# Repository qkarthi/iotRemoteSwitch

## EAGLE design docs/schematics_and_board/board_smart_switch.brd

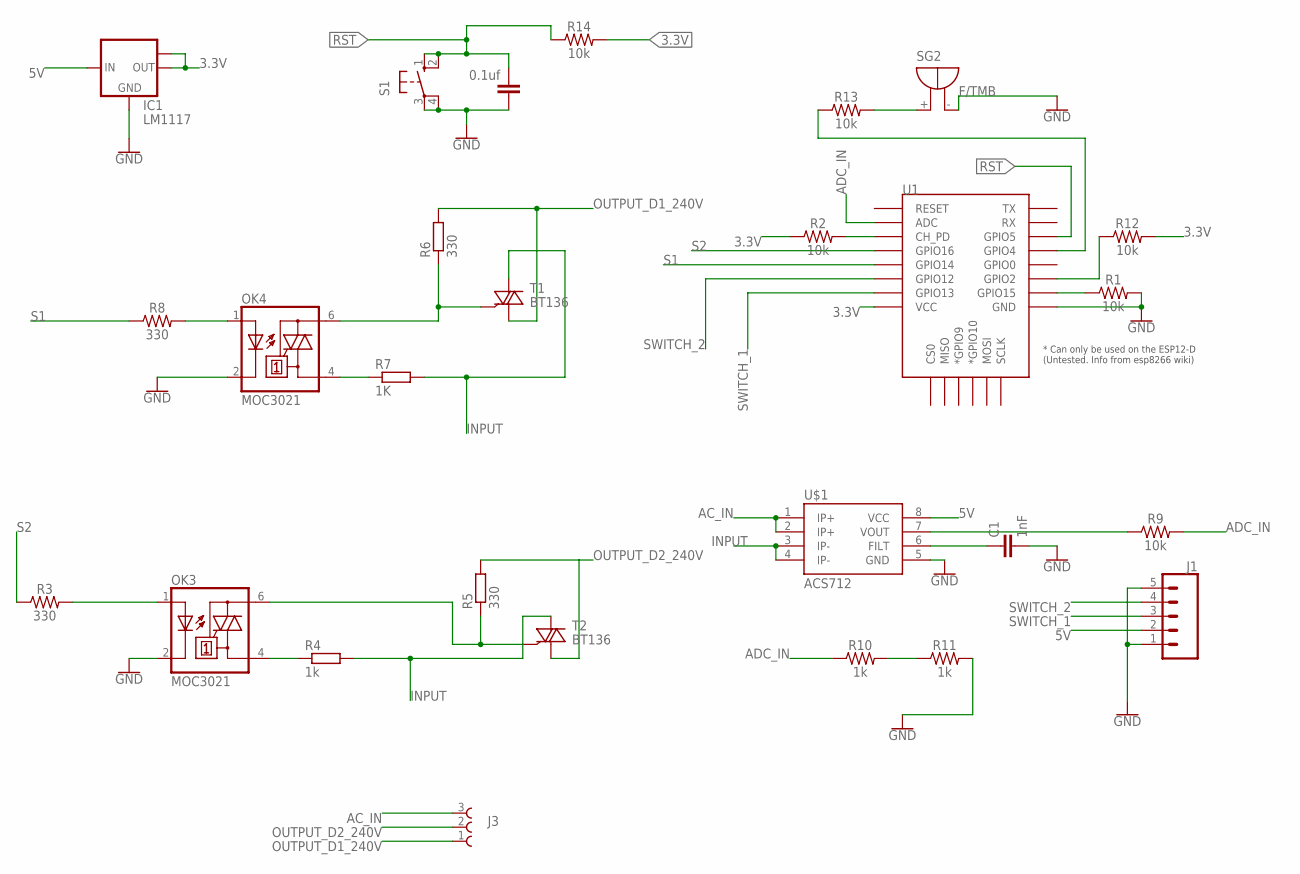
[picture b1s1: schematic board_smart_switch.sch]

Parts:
C1: 1nF; 0805
C2: 0.1uf; 0805
IC1: LM1117; SOT223
J1: CONN_05JST; JST-5-PTH
J3: 691104700003
OK3, OK4: MOC3021; DIL6-SMD
R1, R2, R9, R12, R13, R14: 10k; 0805
R3, R8: 330; 0805
R4: 1k; R2512
R5, R6: 330; R2512
R7: 1K; R2512
R10, R11: 1k; 0805
S1: 10-XX; B3F-10XX
SG2: F/TMB
T1, T2: BT136; TO220AB
U1: ESP12ESMD; ESP12E-SMD
U$1: ACS712; SO08

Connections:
3.3V: IC1.2 (OUT), IC1.TAB (OUT1), R2.1, R12.2, R14.2, U1.VCC
5V: IC1.3 (IN), J1.2, U$1.8 (VCC)
AC_IN: J3.3 (1), U$1.1 (IP+), U$1.2 (IP+)
ADC_IN: R9.2, R10.1, U1.ADC
GND: C1.2, C2.1, IC1.1 (GND), J1.1, J1.5, OK3.2 (C), OK4.2 (C), R1.2, R11.2, S1.3, S1.4 (P1), SG2.-, U1.GND, U$1.5 (GND)
INPUT: R4.2, R7.2, T1.2 (A2), T2.2 (A2), U$1.3 (IP-), U$1.4 (IP-)
unnamed: OK4.1 (A), R8.2
unnamed: OK3.1 (A), R3.2
unnamed: R2.2, U1.CH_PD
unnamed: R1.1, U1.GPIO15
unnamed: OK4.4 (A1), R7.1
unnamed: OK3.6 (A2), R5.1, T2.3 (G)
unnamed: C1.1, U$1.6 (FILT)
unnamed: OK3.4 (A1), R4.1
unnamed: OK4.6 (A2), R6.1, T1.3 (G)
unnamed: R9.1, U$1.7 (VOUT)
unnamed: R10.2, R11.1
unnamed: R12.1, U1.GPIO2
unnamed: R13.2, SG2.+
unnamed: R13.1, U1.GPIO4
OUTPUT_D1_240V: J3.1 (3), R6.2, T1.1 (A1)
OUTPUT_D2_240V: J3.2, R5.2, T2.1 (A1)
RST: C2.2, R14.1, S1.1 (S), S1.2 (S1), U1.GPIO5
S1: R8.1, U1.GPIO14
S2: R3.1, U1.GPIO16
SWITCH_1: J1.3, U1.GPIO13
SWITCH_2: J1.4, U1.GPIO12

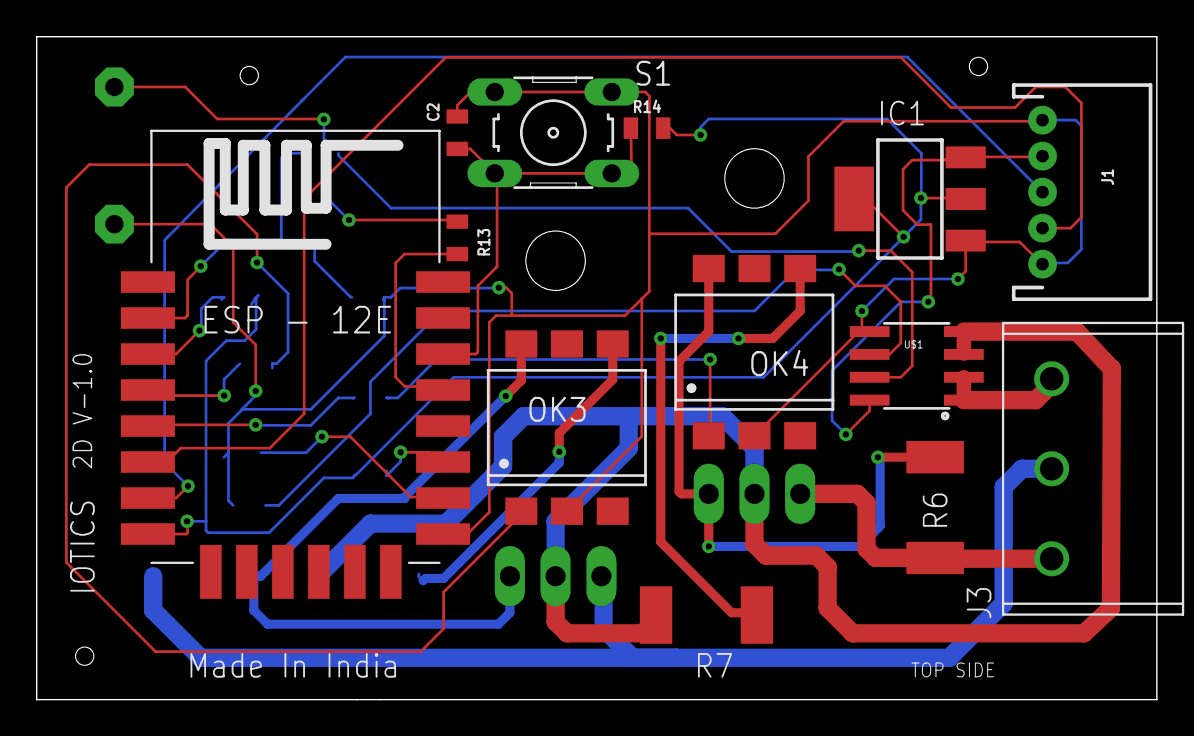
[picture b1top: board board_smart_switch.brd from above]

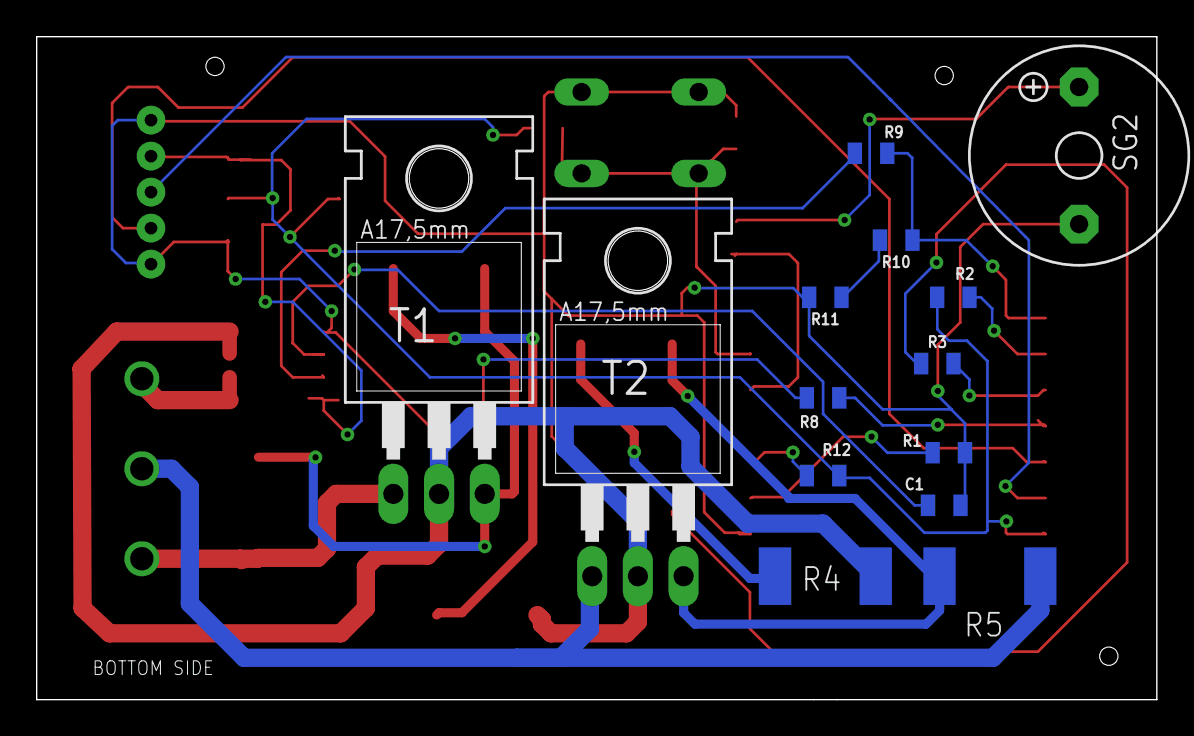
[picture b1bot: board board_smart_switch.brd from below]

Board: 2 copper layers, 62.2 x 36.8 mm, 27 parts (14 on the bottom side), 27 nets.

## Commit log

2017-08-04 Initial commit to repo
2017-08-04 added to git
2017-08-04 board_details
2017-08-08 RESET CODE
2017-08-08 RESET CODE successfully integrated
2017-08-08 RESET CODE updated
2017-08-18 commented
2017-08-21 unit/watts calculation
2017-08-28 new file testing
2017-08-28 new text
2017-08-28 buzzer code added
2017-08-29 buzzer code added and verified
2017-09-02 upto date
2017-09-06 code bare esp8266
2017-09-08 schedular_user_informative
2017-09-11 schedular_rev_1
2017-09-12 bare medium firmware v 1.0
2017-09-12 error rectified on scheduling
2017-09-14 kw hr calculation with reset
2017-09-19 mac address to wifi ssid
2017-10-06 karthik upto date all codes
2017-10-09 reset prevention
2017-10-11 alpha_version_firmware_cloud_rtc
2017-10-20 arduino and esp combination via serial slazer
2018-03-05 Added Templeate ID and variable
2018-04-23 New repo initialized
2018-04-23 directory removed
2018-05-05 Blynk connection check
2018-05-07 Refactor code for offline devices
2018-05-07 dump switch state to device
2018-05-08 dump mode real time code added
2018-05-08 last memory state of device retained
2018-05-08 switch state changer identification
2018-05-09 dump + last state + reset
2018-05-09 timeout for ap mode
2018-05-09 timeout for ap mode correction
2018-05-10 added disconnection and blynk reconnection code
2018-05-11 rssi + status icon + scheduling + wifi timeadjust )
2018-05-15 disabled wifi cloud checking
2018-05-15 last state added to branch
2018-05-15 2.4.1 library finished
2018-05-16 device s=tiles status fixed
2018-05-22 hard code for single device
2018-05-22 device show for upnp
2018-05-22 working for one device - cleaned after removing wrong functions
2018-05-23 added codes in linear method
2018-05-23 alexa working with blynk for 2 devices
2018-05-23 alexa functions completed and checked
2018-05-24 updated wemo switch serial number
2018-05-28 string for bulb is introduced
2018-05-29 device renaming via text box
2018-06-11 debug code enhanced
2018-07-16 vendor,board,firmware changed
2018-07-23 code upgrade
2019-04-22 migrated to github

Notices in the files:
parts and their libraries:
SparkFun-Capacitors: Licensing: Creative Commons ShareAlike 4.0 International - https://creativecommons.org/licenses/by-sa/4.0
EAGLE-TERMINAL_BLOCKS-rev17a: Copyright: Würth Elektronik
